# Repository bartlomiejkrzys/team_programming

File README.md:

# (TeamProgramming) MakeChart

## Requirements:
* Python 3.X
* matplotlib :
  ```
  console >> python -m pip install matplotlib
  ```

## Usage:
* Enter project directory.
* Type :
  ```
  console >> python make_chart.py filename
  ```

#### Example with available file :
   ```
 	console >> python make_chart.py EEPROM
   ```

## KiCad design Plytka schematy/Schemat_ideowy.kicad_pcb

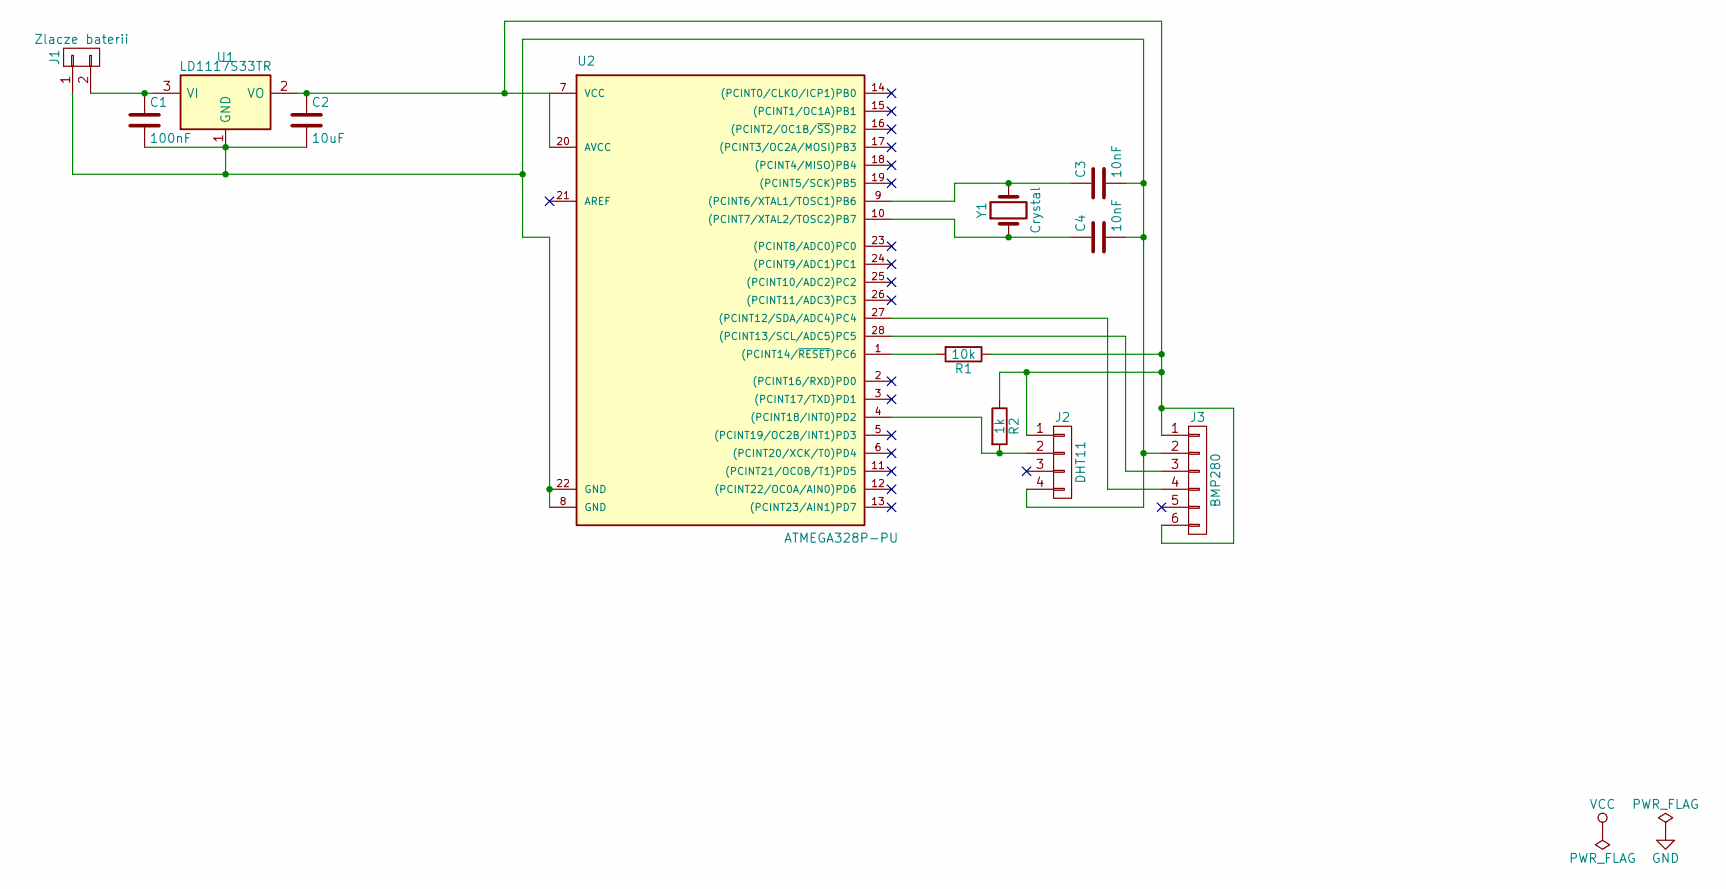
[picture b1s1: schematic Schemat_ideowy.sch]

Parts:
C1: 100nF; C_Axial_L3.8mm_D2.6mm_P7.50mm_Horizontal
C2: 10uF; C_Axial_L3.8mm_D2.6mm_P7.50mm_Horizontal
C3, C4: 10nF; C_Axial_L3.8mm_D2.6mm_P7.50mm_Horizontal
J1: Zlacze baterii; Pin_Header_Angled_1x02_Pitch2.54mm
J2: DHT11; Pin_Header_Angled_1x04_Pitch2.54mm
J3: BMP280; Pin_Header_Angled_1x06_Pitch2.54mm
R1: 10k; R_Axial_DIN0207_L6.3mm_D2.5mm_P10.16mm_Horizontal
R2: 1k; R_Axial_DIN0207_L6.3mm_D2.5mm_P10.16mm_Horizontal
U1: LD1117S33TR; TO-218_SOT93_Vertical
U2: ATMEGA328P-PU; DIP-28_W7.62mm_Socket_LongPads
Y1: Crystal; Crystal_HC18-U_Vertical

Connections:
unnamed: C1.1, J1.2, U1.3 (VI)
unnamed: C1.2, C2.2, C3.2, C4.2, J1.1, J2.4, J3.2, U1.1 (GND), U2.8 (GND), U2.22 (GND)
unnamed: C2.1, J2.1, J3.1, J3.6, R1.1, R2.1, U1.2 (VO), U2.7 (VCC), U2.20 (AVCC)
unnamed: C3.1, U2.9 ((PCINT6/XTAL1/TOSC1)PB6), Y1.2
unnamed: C4.1, U2.10 ((PCINT7/XTAL2/TOSC2)PB7), Y1.1
unnamed: J2.2, R2.2, U2.4 ((PCINT18/INT0)PD2)
unnamed: J3.3, U2.28 ((PCINT13/SCL/ADC5)PC5)
unnamed: J3.4, U2.27 ((PCINT12/SDA/ADC4)PC4)
unnamed: R1.2, U2.1 ((PCINT14/~RESET~)PC6)

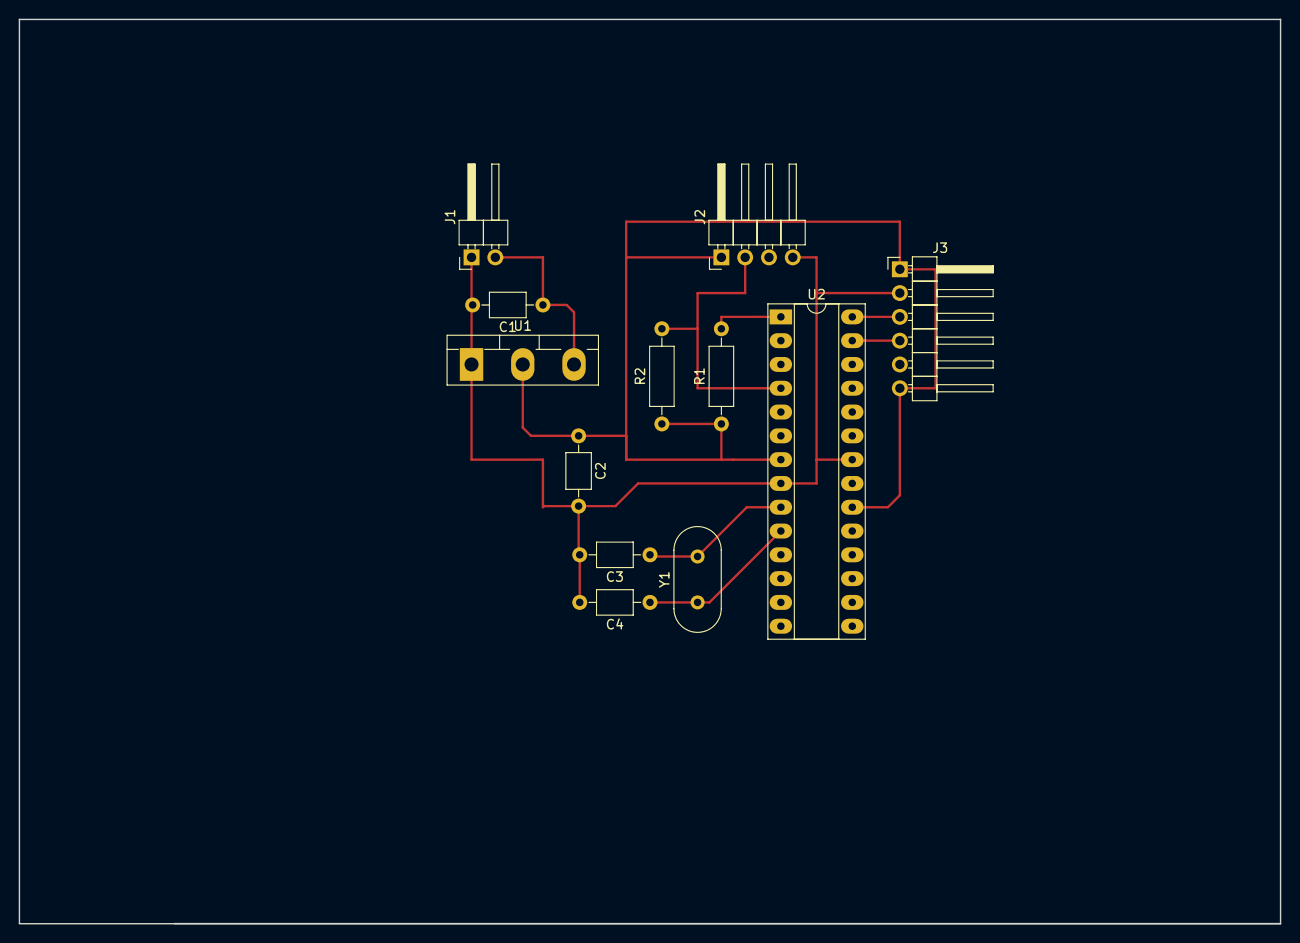
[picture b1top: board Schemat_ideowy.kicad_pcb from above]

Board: 2 copper layers, 134.6 x 96.5 mm, 12 parts (0 on the bottom side), 9 nets.

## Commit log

2017-03-28 Added index.html, created server handling JSON for retrieving data
2017-03-28 Added requirements.ini file
2017-03-28 Changed string formatting in id_out_of_range_msg to use new style .format
2017-05-31 Small changes
2017-05-31 poprawione przeliczanie wysokosci
2017-05-31 poprawiony plik README.md
2017-05-31 dodanie plikow zwiazanych z elektronika
2017-06-04 Added docstrings + refactored a bit of plotting code
2017-06-04 Last docstring
2017-06-04 typo fix
2017-06-04 aktualizacja opisu projektu
